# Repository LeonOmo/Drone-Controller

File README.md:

# Custom DIY Drone Controller

A custom ESP32-based drone remote controller designed from scratch.

## Features
- ESP32 Wroom: Microcontroller
- ExpressLRS / CRSF Protocol: Serial communication (420 kbaud) via RadioMaster RP1 module.
- Live OLED Telemetry: signal strength, battery status, altitude and speed
- Custom Control Inputs:
  - 2x Dual-axis Joysticks (Roll, Pitch, Yaw, Throttle)
  - 5x Toggle Switches (Arm, Flight Mode, Buzzer, Landing Gear, Folding Arms)
  - 3x Potentiometers (Motor Caps & 1/2 & 3/4 Motor Cap)
  - Hardware Status LEDs (Arm, Landing Gear, Link Status)

## CAD Model
- Designed from scratch in Onshape.

## PCB & Schematic
- Designed in KiCad.

## BOM
- ESP32-WROOM-32E Modul
- Voltage Regulator: AMS1117-3.3
- USB Connector: 16-Pin Female USB-C Receptacle
- RadioMaster RP1 ELRS Transmitter/Receiver Module
- 0.96" SSD1306 I2C OLED Display
- 2x PS2 Joysticks
- 5x MTS-102-A2 Toggle Switches
- 3x R-0904N-L-25KS Potentiometers
- 3x LEDs
- 1x Custom 3D Printed Enclosure
- 8x Resisitor (3x 220, 6x 10k, 2x 5,1k)
- 3x Capacitor (2x 100nF, 1x 10uF)
- Male Pin Headers (2.54 mm Pitch: 1x 1x4 Pin, 2x 1x5 Pin)
- Female Pin Headers (2.54 mm: 1x 1x4)

## Firmware Setup
Built with PlatformIO in Visual Studio Code.

## Extra Stuff
Please tell me if my funding request is too high i think i asked for too much.

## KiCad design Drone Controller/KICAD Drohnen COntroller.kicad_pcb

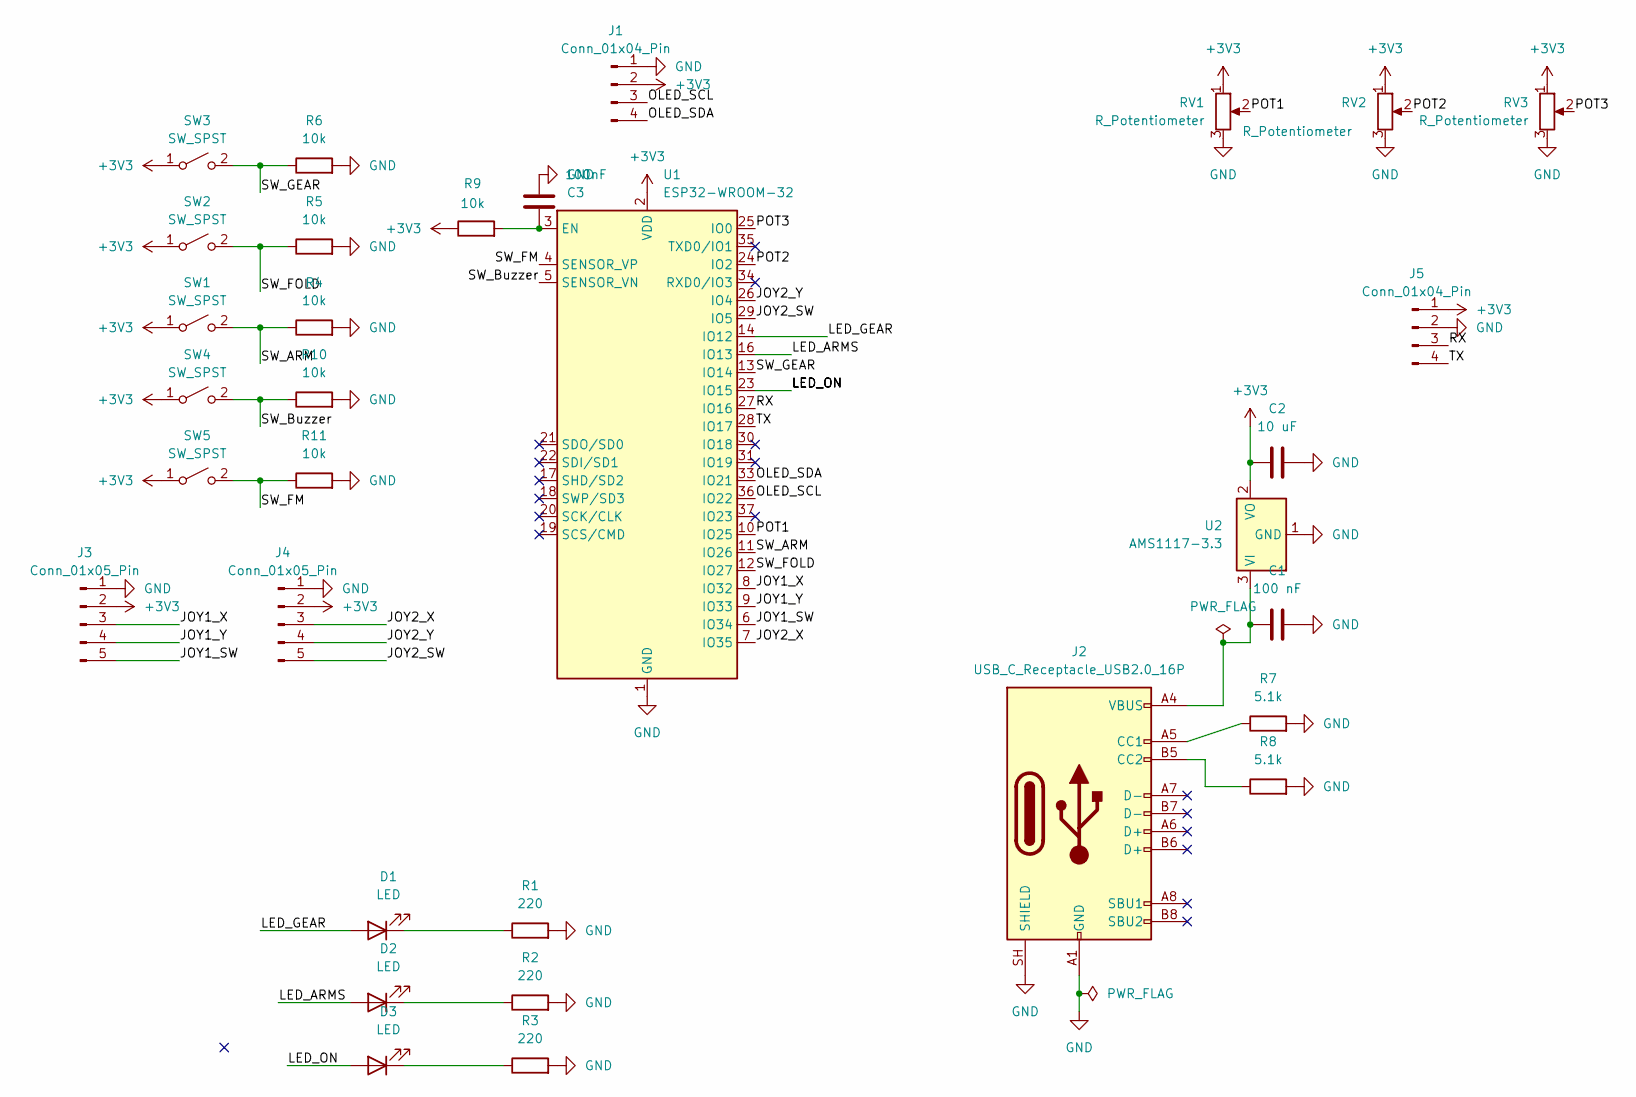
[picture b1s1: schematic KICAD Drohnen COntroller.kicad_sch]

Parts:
C1: 100 nF; CP_Radial_D5.0mm_P2.50mm
C2: 10 uF; CP_Radial_D5.0mm_P2.00mm
C3: 100nF; CP_Radial_D5.0mm_P2.50mm
D1, D2, D3: LED; LED_D3.0mm
J1, J5: Conn_01x04_Pin; PinHeader_1x04_P2.54mm_Vertical
J2: USB_C_Receptacle_USB2.0_16P; USB_C_Receptacle_HRO_TYPE-C-31-M-12
J3, J4: Conn_01x05_Pin; PinHeader_1x05_P2.54mm_Vertical
R1, R2, R3: 220; R_Axial_DIN0207_L6.3mm_D2.5mm_P7.62mm_Horizontal
R4, R5, R6, R9, R10, R11: 10k; R_Axial_DIN0207_L6.3mm_D2.5mm_P7.62mm_Horizontal
R7, R8: 5.1k; R_Axial_DIN0207_L6.3mm_D2.5mm_P7.62mm_Horizontal
RV1, RV2, RV3: R_Potentiometer; Potentiometer_Bourns_PTV09A-1_Single_Vertical
SW1, SW2, SW3, SW4, SW5: SW_SPST; SW_100SP1T1B4M2QE
U1: ESP32-WROOM-32
U2: AMS1117-3.3; R_0805_2012Metric

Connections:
+3V3: C2.1, J1.2, J3.2, J4.2, J5.1, R9.1, RV1.1, RV2.1, RV3.1, SW1.1 (A), SW2.1 (A), SW3.1 (A), SW4.1 (A), SW5.1 (A), U1.2 (VDD), U2.2 (VO)
/JOY1_SW: J3.5, U1.6 (IO34)
/JOY1_X: J3.3, U1.8 (IO32)
/JOY1_Y: J3.4, U1.9 (IO33)
/JOY2_SW: J4.5, U1.29 (IO5)
/JOY2_X: J4.3, U1.7 (IO35)
/JOY2_Y: J4.4, U1.26 (IO4)
/LED_ARMS: D2.2 (A), U1.16 (IO13)
/LED_GEAR: D1.2 (A), U1.14 (IO12)
/LED_ON: D3.2 (A), U1.23 (IO15)
/OLED_SCL: J1.3, U1.36 (IO22)
/OLED_SDA: J1.4, U1.33 (IO21)
/POT1: RV1.2, U1.10 (IO25)
/POT2: RV2.2, U1.24 (IO2)
/POT3: RV3.2, U1.25 (IO0)
/RX: J5.3, U1.27 (IO16)
/SW_ARM: R4.1, SW1.2 (B), U1.11 (IO26)
/SW_Buzzer: R10.1, SW4.2 (B), U1.5 (SENSOR_VN)
/SW_FM: R11.1, SW5.2 (B), U1.4 (SENSOR_VP)
/SW_FOLD: R5.1, SW2.2 (B), U1.12 (IO27)
/SW_GEAR: R6.1, SW3.2 (B), U1.13 (IO14)
/TX: J5.4, U1.28 (IO17)
GND: C1.2, C2.2, C3.1, J1.1, J2.A1 (GND), J2.A12 (GND), J2.B1 (GND), J2.B12 (GND), J2.SH (SHIELD), J3.1, J4.1, J5.2, R1.2, R2.2, R3.2, R4.2, R5.2, R6.2, R7.2, R8.2, R10.2, R11.2, RV1.3, RV2.3, RV3.3, U1.1 (GND), U1.15 (GND), U1.38 (GND), U1.39 (GND), U2.1 (GND)
unnamed: D1.1 (K), R1.1
unnamed: D2.1 (K), R2.1
unnamed: D3.1 (K), R3.1
unnamed: J2.A5 (CC1), R7.1
unnamed: J2.B5 (CC2), R8.1
unnamed: C3.2, R9.2, U1.3 (EN)
unnamed: C1.1, J2.A4 (VBUS), J2.A9 (VBUS), J2.B4 (VBUS), J2.B9 (VBUS), U2.3 (VI)

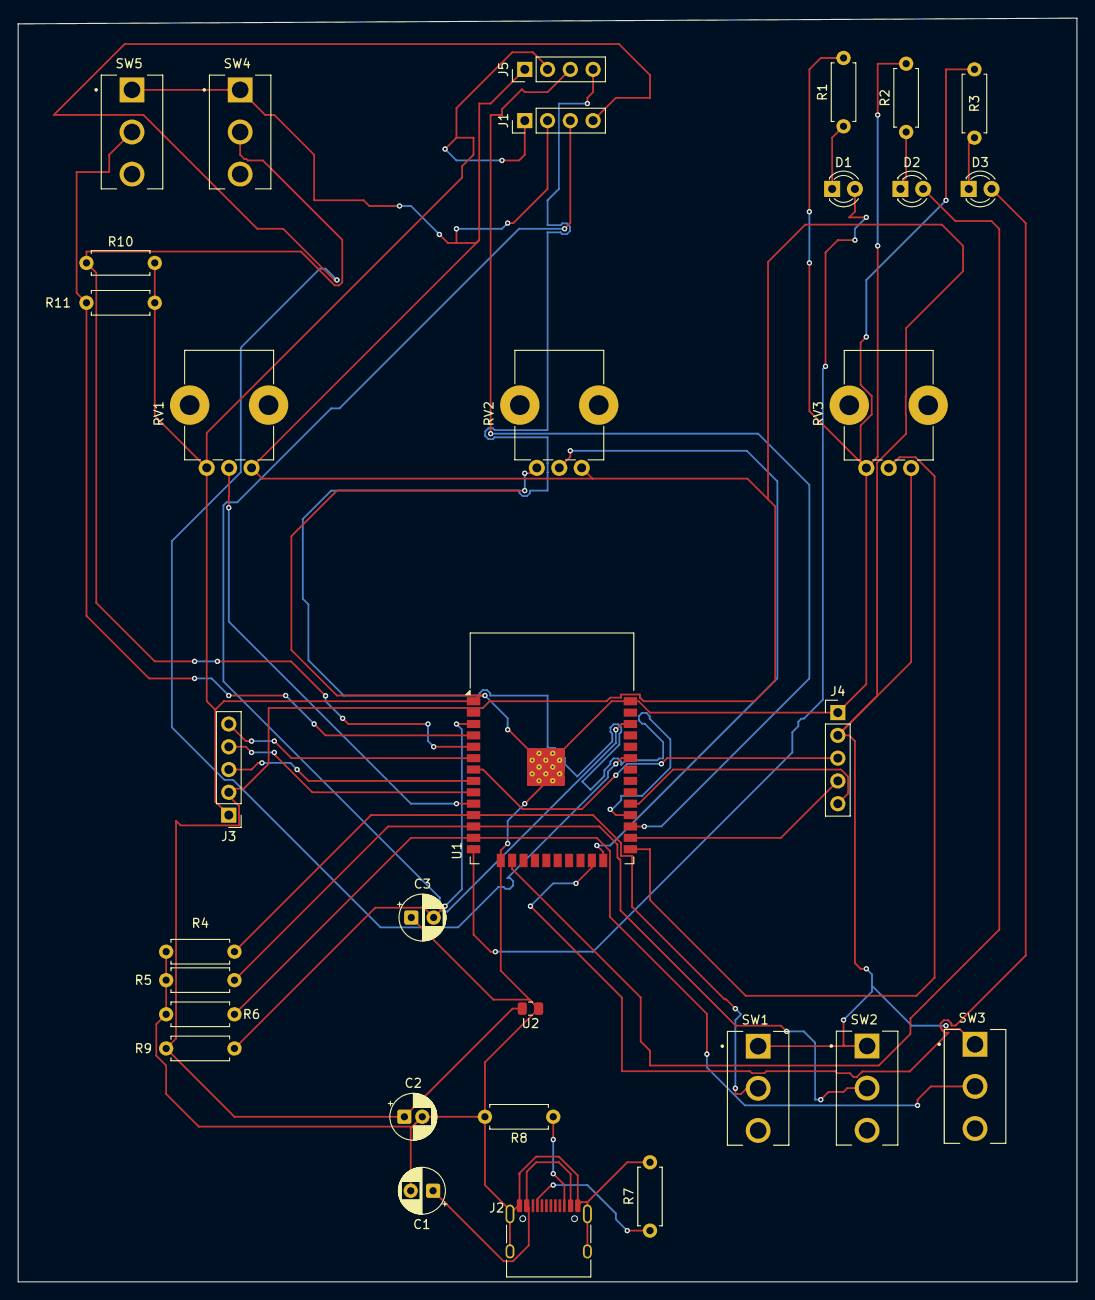
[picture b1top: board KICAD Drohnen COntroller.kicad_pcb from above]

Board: 2 copper layers, 118.1 x 141.0 mm, 32 parts (0 on the bottom side), 30 nets.

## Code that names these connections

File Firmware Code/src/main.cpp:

#include <Arduino.h>
#include <Wire.h>
#include <Adafruit_GFX.h>
#include <Adafruit_SSD1306.h>
#include <AlfredoCRSF.h>

#define JOY1_X 32
#define JOY1_Y 33
#define JOY1_SW 34
#define JOY2_X 35
#define JOY2_Y 4
#define JOY2_SW 5

#define POT1 25
#define POT2 2
#define POT3 0

#define SW_FM 36
#define SW_Buzzer 39
#define SW_GEAR 14
#define SW_ARM 26
#define SW_FOLD 27

#define LED_GEAR 12
#define LED_ARMS 13
#define LED_ON  15

#define OLED_SCL 22
#define OLED_SDA 21
#define SCREEN_WIDTH 128
#define SCREEN_HEIGHT 64

#define RX 16
#define TX 17 

Adafruit_SSD1306 display(SCREEN_WIDTH, SCREEN_HEIGHT, &Wire, -1);
AlfredoCRSF crsf;

void setup() {
  Serial.begin(115200);

  pinMode(SW_FM, INPUT);
  pinMode(SW_Buzzer, INPUT);
  pinMode(SW_GEAR, INPUT_PULLUP);
  pinMode(SW_ARM, INPUT_PULLUP);
  pinMode(SW_FOLD, INPUT_PULLUP);
  pinMode(JOY1_SW, INPUT_PULLUP);
  pinMode(JOY2_SW, INPUT_PULLUP);

  pinMode(LED_ARMS, OUTPUT);
  pinMode(LED_GEAR, OUTPUT);
  pinMode(LED_ON, OUTPUT);

  digitalWrite(LED_ARMS, LOW);
  digitalWrite(LED_GEAR, LOW);
  digitalWrite(LED_ON, LOW);

  Wire.begin(OLED_SDA, OLED_SCL);
  if (!display.begin(SSD1306_SWITCHCAPVCC, 0x3C)) {
    Serial.println("OLED Display was not found!"); 
  } else {
    display.clearDisplay();
    display.setTextColor(WHITE);
    display.setTextSize(1);
    display.setCursor(5, 0);
    display.println("OMO SYSTEMS");
    display.setCursor(5, 15);
    display.println("Connecting RP1...");
    display.setCursor(5, 30);
    display.println("Welcome!");
    display.display();
    delay(2000);
  }

  Serial1.begin(420000, SERIAL_8N1, RX, TX);
  crsf.begin(Serial1);
}

void loop() {
  int roll     = map(analogRead(JOY1_X), 0, 4095, 191, 1792);
  int pitch    = map(analogRead(JOY1_Y), 0, 4095, 191, 1792);
  int yaw      = map(analogRead(JOY2_X), 0, 4095, 191, 1792);
  int throttle = map(analogRead(JOY2_Y), 0, 4095, 191, 1792);

  int Pot1Val = map(analogRead(POT1), 0, 4095, 191, 1792);
  int Pot2Val = map(analogRead(POT2), 0, 4095, 191, 1792);
  int Pot3Val = map(analogRead(POT3), 0, 4095, 191, 1792);

  int swFm     = (digitalRead(SW_FM) == LOW)     ? 1792 : 191;
  int swBuzzer = (digitalRead(SW_Buzzer) == LOW) ? 1792 : 191;
  int swGear   = (digitalRead(SW_GEAR) == LOW)   ? 1792 : 191;
  int swArm    = (digitalRead(SW_ARM) == LOW)    ? 1792 : 191;
  int swFold   = (digitalRead(SW_FOLD) == LOW)   ? 1792 : 191;

  digitalWrite(LED_ARMS, (swArm == 1792) ? HIGH : LOW);
  digitalWrite(LED_GEAR, (swGear == 1792) ? HIGH : LOW);
  bool isConnected = crsf.isLinkUp();
  digitalWrite(LED_ON, isConnected ? HIGH : LOW);

  crsf_channels_t crsfChannels;
  crsfChannels.ch0  = roll;
  crsfChannels.ch1  = pitch;
  crsfChannels.ch2  = throttle;
  crsfChannels.ch3  = yaw;
  crsfChannels.ch4  = swArm;
  crsfChannels.ch5  = swFm;
  crsfChannels.ch6  = swBuzzer;
  crsfChannels.ch7  = swGear;
  crsfChannels.ch8  = swFold;
  crsfChannels.ch9  = Pot1Val;
  crsfChannels.ch10 = Pot2Val;
  crsfChannels.ch11 = Pot3Val;

  crsf.writeChannels(0xC8, &crsfChannels);
  crsf.update();

  static unsigned long lastDisplayUpdate = 0;
  if (millis() - lastDisplayUpdate > 100) {
    lastDisplayUpdate = millis();
    
    display.clearDisplay();
    display.setCursor(0, 0);
    display.print("OMO");
    display.println(isConnected ? "[CONNECTED]" : "[NO SIGNAL]");
    display.println("--------------");

    float batteryVolts = 15.8;
    int rssi = isConnected ? crsf.getLinkStatistics()->active_antenna : 0;
    int speedKmH = 0;
    int altitudeMeters = 0;

    display.printf("Bat: %.1fV | Sig: %d%%\n", batteryVolts, rssi);
    display.printf("Alt: %dm   | Spd: %dkm/h\n", altitudeMeters, speedKmH);
    display.println("--------------");

    display.printf("ARM: %s | GEAR: %s\n", 
                   (swArm == 1792) ? "ON " : "OFF",
                   (swGear == 1792) ? "DOWN" : "UP");
    display.display();
  }
}
